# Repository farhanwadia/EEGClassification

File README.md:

# Brain Computer Interfaces for Industrial Fluid Flow Control

## Group Members
**Amaani Zuberi**

**Farhan Wadia**

**Jun Sung Park**

**Mrinal Jha** 

**Stephanie DiNunzio**

## Description
This repository consists of all data and software developed for our capstone project.

Programs for collecting EEG data based on covert speech, motor imagery, SSVEP, and eye movements can be found in the `Data Collection Scripts` folder. Follow the instructions in the `Using the Muse Headset for Collecting Raw EEG Signals.pdf` file within that folder to run any of the programs. Note that the MuseLab SDK is not included in this folder and will need to be installed separately.

Raw data files we collected for covert speech model training can be found in the `Nov 2020 Raw Data` and `Feb 2021 Raw Data` folders.

Filtering, time series data outputs, FFT outputs, wavelet transforms, and corresponding graphs were all developed using the `visualization.py` script. Outputs can be found organized in the `Nov 2020 Filtered Data` and `Feb 2021 Filtered Data` folders. 

Model training can be found in the `EEG_Classification_Model_Training.ipynb` notebook. Downloaded model weight files can be found in the `Trained Model Weights` folder. Testing for these models is conducted in the `EEG_Classification_Model_Testing.ipynb` notebook. A breakdown of the results for our final chosen model can be found in the `Final Model Test Results Summary.xlsx` spreadsheet.

Relevant files for implementing the chosen model live in conjunction with a solenoid valve can be found in the `Final Prototype Implementation` folder. Refer to the `Using the Muse Headset for Collecting Raw EEG Signals.pdf` file for further instructions on how to set up the Muse for live EEG streaming, and also refer to `Implementation_README.md`

The `Prototype and Final Design CAD Assemblies` folder contains SOLIDWORKS parts and assemblies showing the mechanical design of our system. The `Electrical Design` folder contains our final and previous versions of the electrical design, and includes the schematic, `.brd` files of the CAD in EAGLE, and `.step` file that can be imported into SOLIDWORKS.

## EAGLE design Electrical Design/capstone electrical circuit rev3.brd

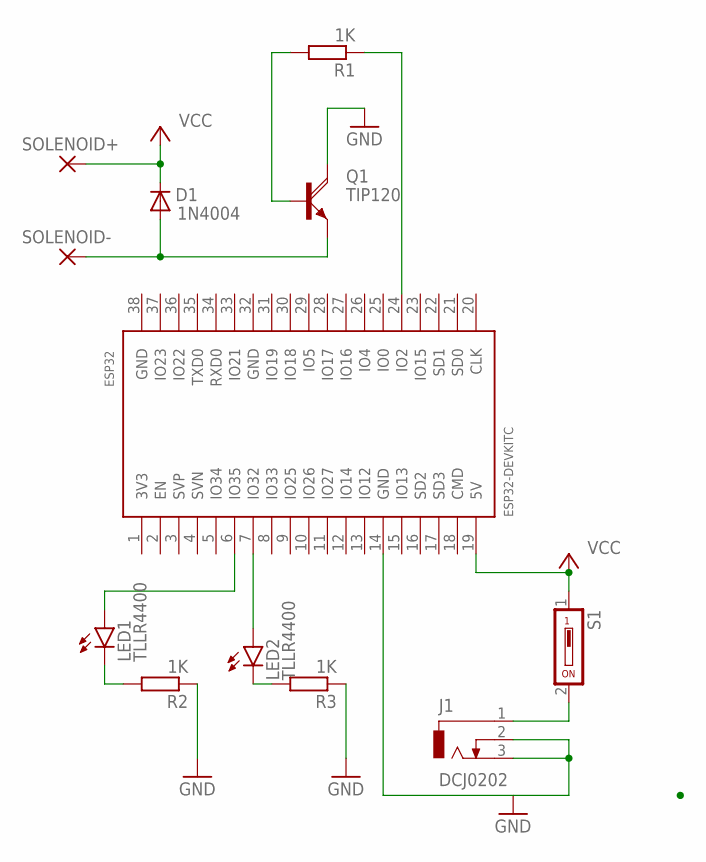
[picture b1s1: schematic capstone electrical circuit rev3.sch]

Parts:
D1: 1N4004; DO41-10
ESP32: ESP32DEVKITC; ESP32-DEVKITC
J1: DCJ0202
LED1, LED2: TLLR4400; LED3MM
Q1: TIP120; TO220AH
R1, R2, R3: 1K; 0207/10
S1: SD4-01
SOLENOID+: WIREPAD2,54/1,0; 2,54/1,0
SOLENOID-: WIREPAD2,54/1,0; 2,54/1,0

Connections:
GND: ESP32.14 (GND), J1.2, J1.3, Q1.C, R2.1, R3.1
unnamed: J1.1, S1.2
unnamed: LED1.K (C), R2.2
unnamed: D1.A, Q1.E, SOLENOID-.1
unnamed: Q1.B, R1.2
unnamed: ESP32.24 (IO2), R1.1
unnamed: LED2.K (C), R3.2
unnamed: ESP32.7 (IO32), LED2.A
unnamed: ESP32.6 (IO35), LED1.A
VCC: D1.C, ESP32.19 (5V), S1.1, SOLENOID+.1

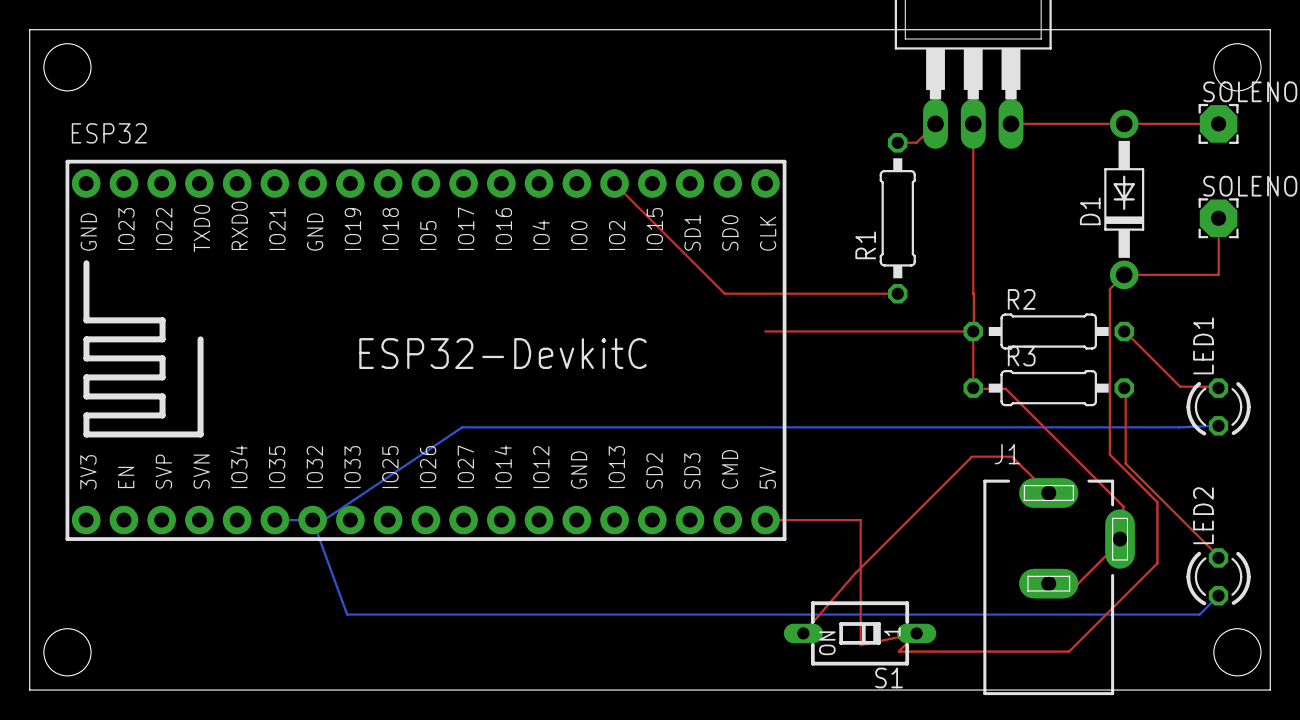
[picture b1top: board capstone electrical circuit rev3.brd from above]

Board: 2 copper layers, 83.5 x 44.4 mm, 12 parts (0 on the bottom side), 10 nets.

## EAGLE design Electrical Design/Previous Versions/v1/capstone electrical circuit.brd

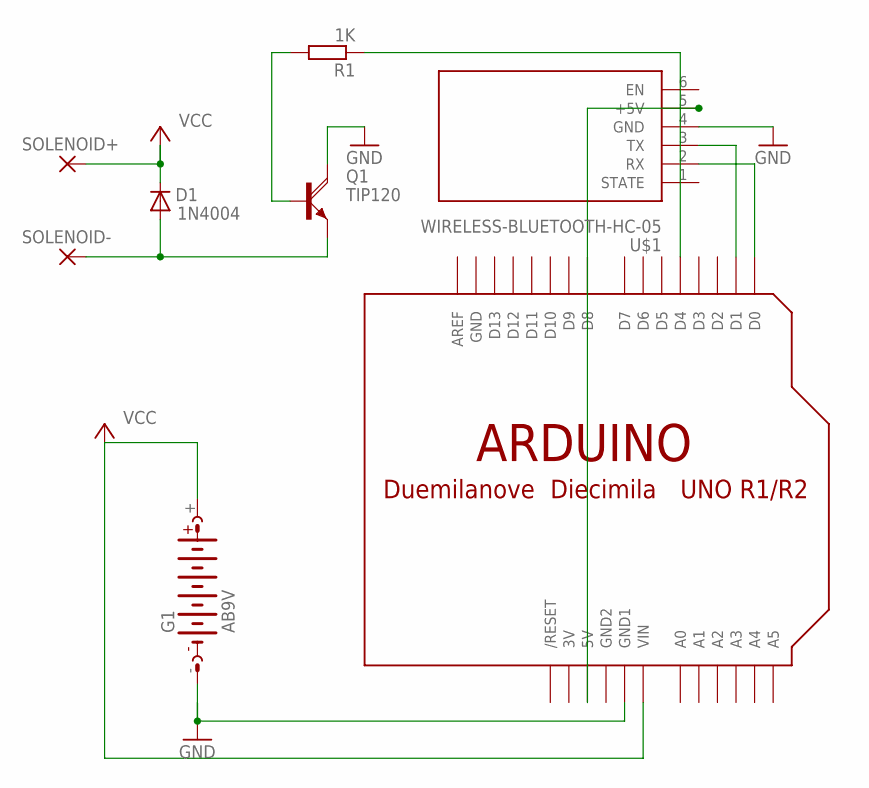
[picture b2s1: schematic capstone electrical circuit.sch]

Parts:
D1: 1N4004; DO41-10
G1: AB9V
Q1: TIP120; TO220AH
R1: 1K; 0207/10
SOLENOID+: WIREPAD2,54/1,0; 2,54/1,0
SOLENOID-: WIREPAD2,54/1,0; 2,54/1,0
U$1: WIRELESS-BLUETOOTH-HC-05
U$2: ARDUINOUNO; ARDUINO

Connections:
3V: U$2.3V
GND: G1.-, Q1.C, U$1.4 (GND), U$2.GND, U$2.GND1
GND2: U$2.GND2
unnamed: U$1.2 (RX), U$2.D0
unnamed: U$1.3 (TX), U$2.D1
unnamed: D1.A, Q1.E, SOLENOID-.1
unnamed: U$1.5 (+5V), U$2.5V
unnamed: Q1.B, R1.2
unnamed: R1.1, U$2.D4
VCC: D1.C, G1.+, SOLENOID+.1, U$2.VIN

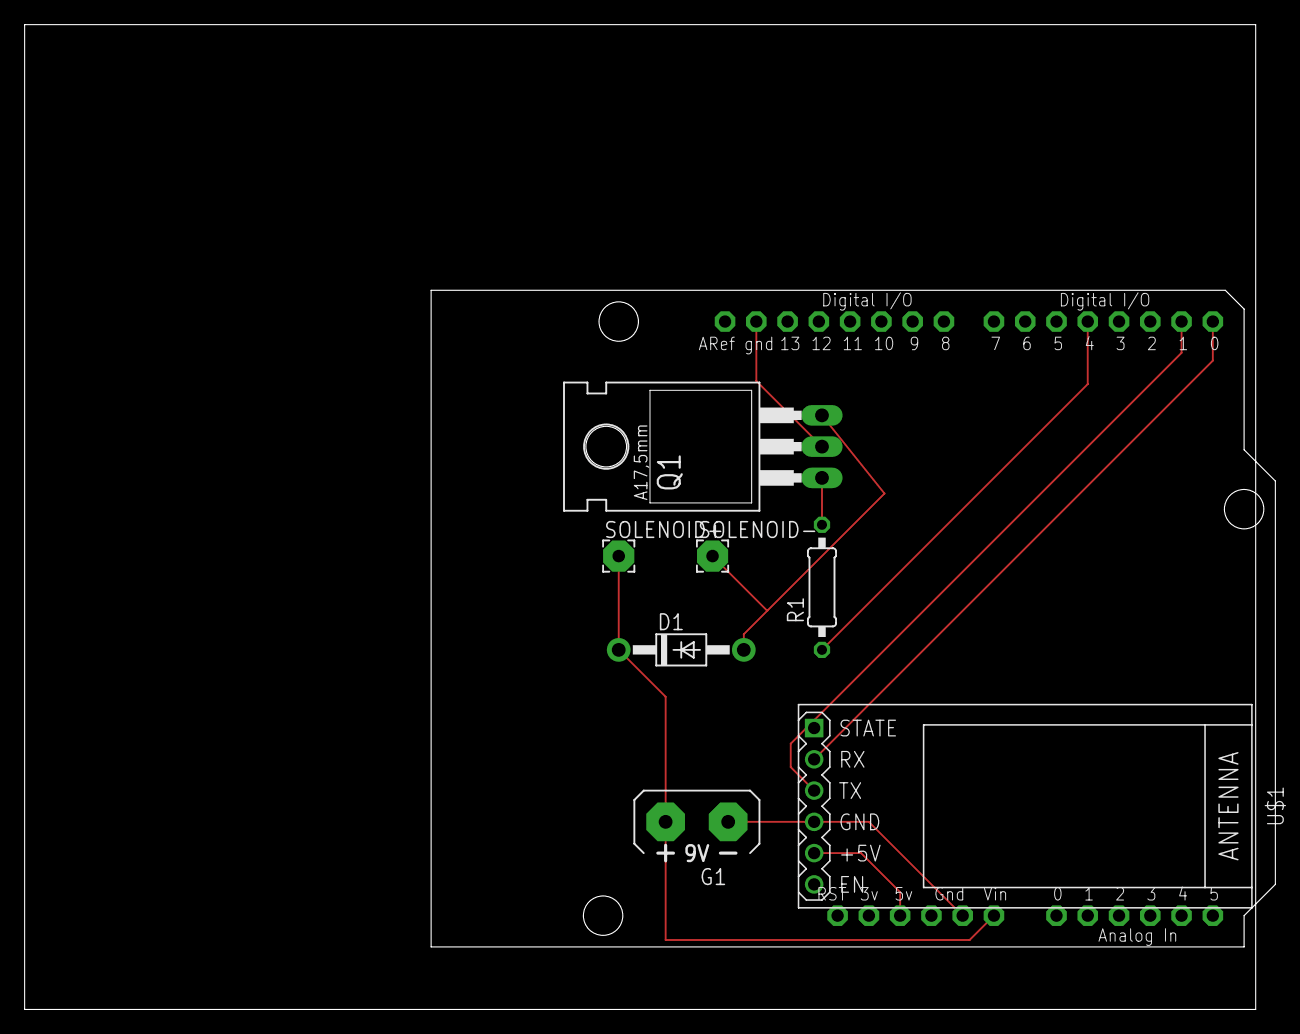
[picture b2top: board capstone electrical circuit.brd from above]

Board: 2 copper layers, 101.6 x 80.0 mm, 8 parts (0 on the bottom side), 8 nets.

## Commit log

2021-02-27 Added Nov 2020 Filtered Data
2021-02-27 Added Feb 2021 Filtered 5s
2021-02-27 Added Feb 2021 Filtered 2 x 3.5s
2021-03-01 Changed folder names for consistency
2021-03-01 Began training with larger dataset of Nov and Feb data
2021-03-15 Trained models and saved best weights to local machine (60-65% val acc)
2021-03-16 Added downloaded model weights after training
2021-03-16 Added testing notebook
2021-03-18 Added discussion. Hard-coded train, val, test splits from training notebook here because of reproducibility issues with trying to do it using np.random.seed
2021-03-18 Added summary results spreadsheet
    Added spreadsheet to show dataset composition and accuracy results segmented by person and class
2021-03-22 Added raw EEG data collection scripts
2021-03-23 Edited Result Table Fonts
2021-03-23 Added code for using model in real-time with valve
2021-03-24 Resolved issue with SVM not loading (was due to using keyword open as a variable name earlier)
2021-03-25 Added README
2021-03-25 Printed out dataset split
2021-03-25 Latest version
2021-03-26 Added CAD Assemblies
2021-03-26 Added mobile app apk

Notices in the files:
parts and their libraries:
diy-modules: Released under the Creative Commons Attribution 4.0 International License: http://creativecommons.org/licenses/by/4.0
